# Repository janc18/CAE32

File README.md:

# CAE32

CAE32 is a project for building and developing all stages of a gaming wheel for PC, specifically for the GNU/Linux operating system.

If you want to contribute, please read the [CONTRIBUTING-english.md](./docs/CONTRIBUTING-english.md) file.

Si tu quieres contribuir, por favor lee el documento [CONTRIBUTING.md](./CONTRIBUTING.md)  

## Overall current status

Developing the UML diagram of the whole system

### PCBs

### Firmware

Working on the development of the UML diagram for the pedals  firmware

### Software

Needed the improvement of compilation and flags for the user interface

## The stages include:

* PCB Design
* Firmware
* Driver (Kernel module if necessary)
* Configuration and calibration through a graphical user interface (GTK-3)
* Design of mechanisms for pedals, gear lever, and wheel
* Power PCB design for feedback motor control (FFB)

### PCB Sponsored by PCBWay

The PCB quality is excellent, the contact with the support service is good, they responded very quickly in the case of any issue, 
and it has a good PCB finish using the STM assembly service,  all the IC pads are correctly soldered. Overall, the total cost of 5 PCBs 
and 2 PCBs with the assembly service is a very accessible, so I will keep using PCBWAY to build the next PCB iterations

[PCBWay Webpage](https://www.pcbway.com/)

## Programming Frameworks and Tools

* Espressif (ESP-IDF)
* STM32CubeIDE
* STM32CubeProgrammer

### User Interface

The interface is developed with the GTK 3 framework, which will allow configurations such as:

* Visualization of data graphically and textually (console)
* Transmission type (Manual, Automatic, Sequential, custom) **Natively**
* Pedal limits, sensitivity
* Pedal type
  * Analog input (Potentiometer, Hall effect, and load cell)
  * SPI, I2C input (Custom sensor)
* Firmware update

## How to compile the project

1. Install all the dependencies
```bash
sudo apt install cmake make gcc pkgconf libevdev-dev libgtk-3-dev libgtk-3-0 libgtest-dev g++
```

2. Run the script to check if all the dependencies was successfully installed
```bash
./Source_code/checking_dependency.sh
```
3. Execute the Makefile to build the graphic interface and the unit tests
```sh
make -C Source_code/
```

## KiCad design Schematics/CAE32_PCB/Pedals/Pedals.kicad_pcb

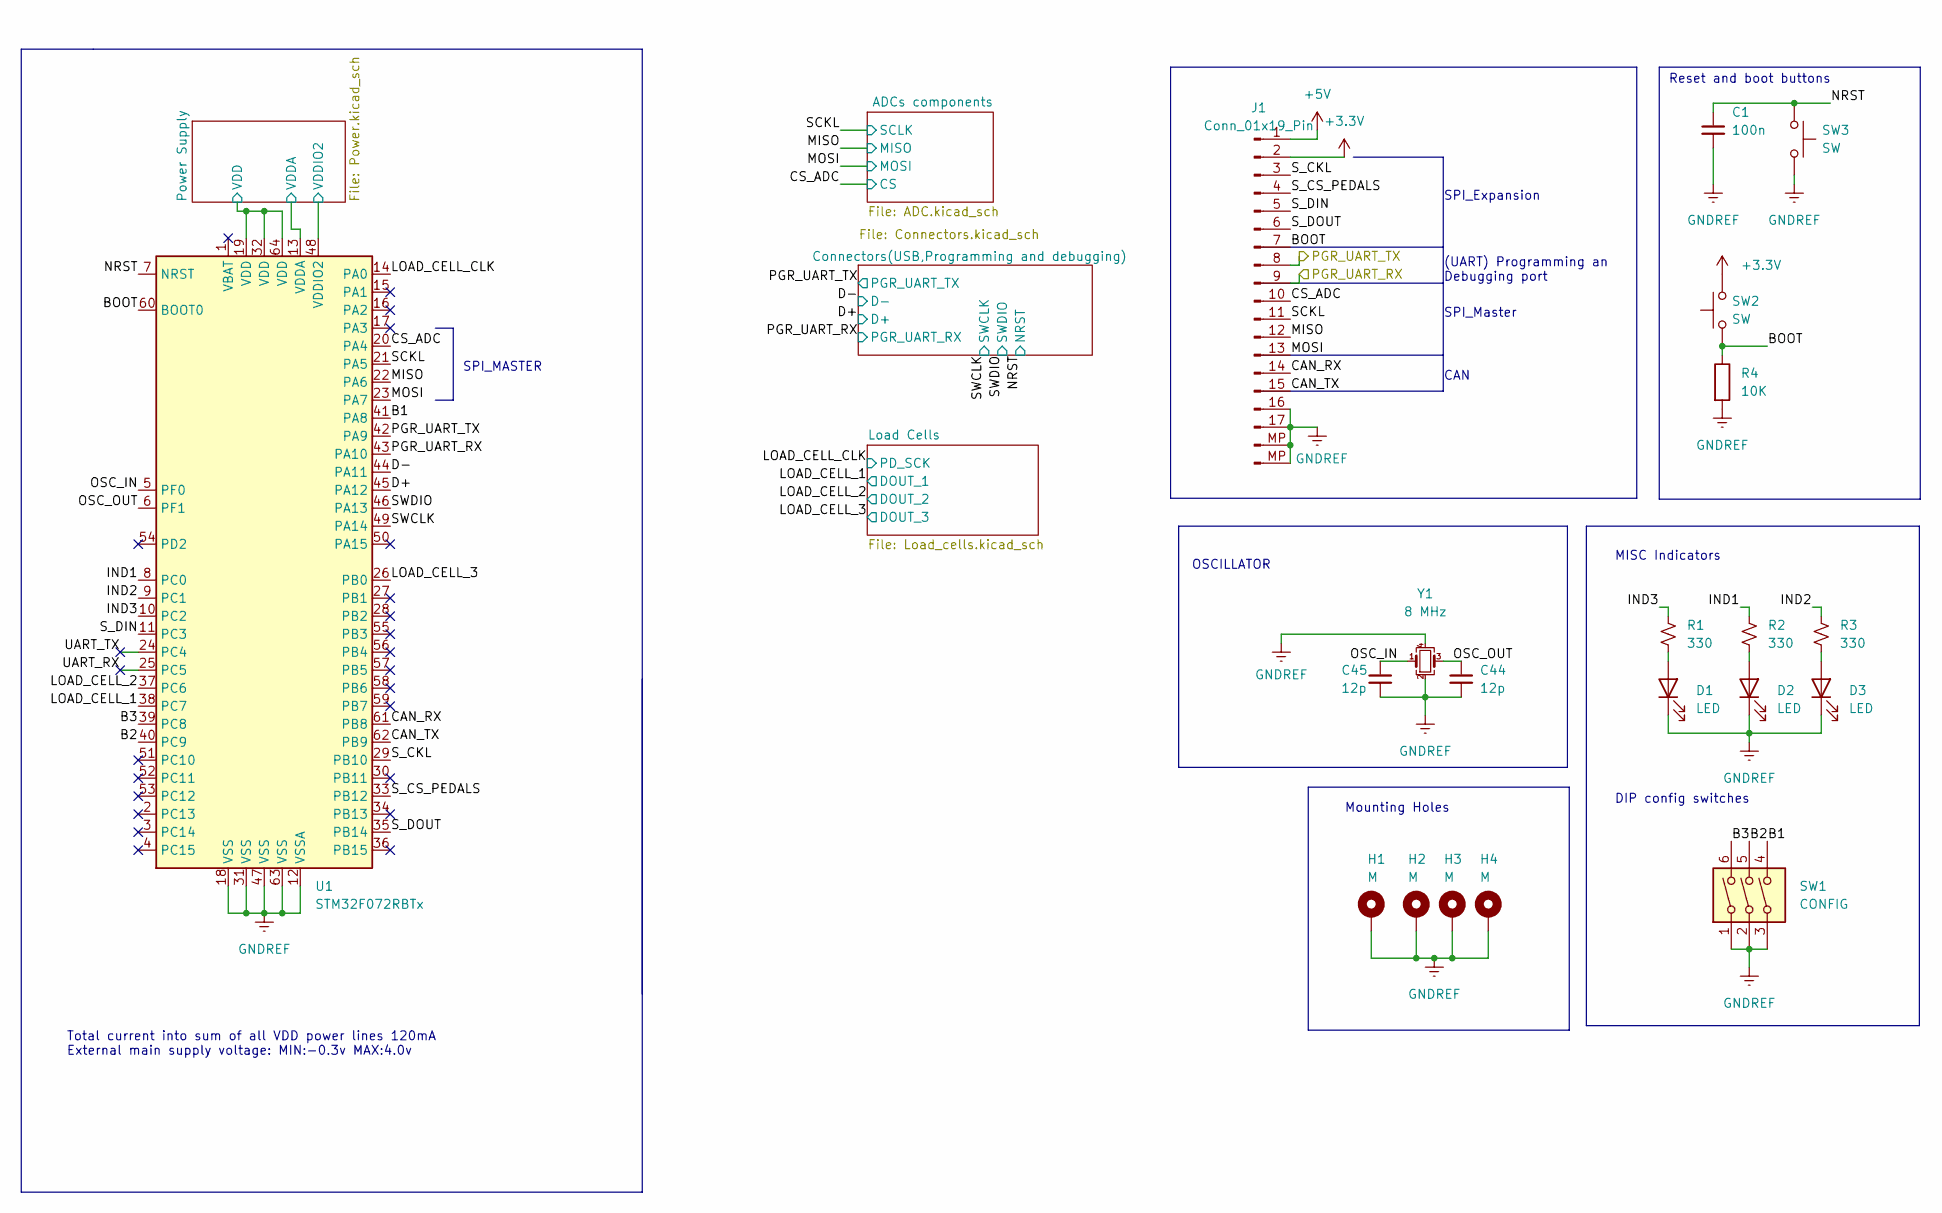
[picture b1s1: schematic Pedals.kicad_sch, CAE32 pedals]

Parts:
C1: 100n; C_0603_1608Metric; LCSC_PART C66501
C44, C45: 12p; C_0603_1608Metric; LCSC_PART C882527
D1, D2, D3: LED; LED_0805_2012Metric; LCSC_PART C965815
H1, H2, H3, H4: M; MountingHole_3.2mm_M3_DIN965_Pad_TopBottom
J1: Conn_01x19_Pin; TE_1-84953-7_1x17-1MP_P1.0mm_Horizontal; LCSC_PART C500176
R1, R2, R3: 330; R_0603_1608Metric; LCSC_PART C21190
R4: 10K; R_0603_1608Metric; LCSC_PART C25804
SW1: CONFIG; SW_DIP_SPSTx03_Slide_KingTek_DSHP03TJ_W5.25mm_P1.27mm_JPin; LCSC_PART C5289932
SW2, SW3: SW; SW_SPST_TL3342; LCSC_PART C2886897
U1: STM32F072RBTx; LQFP-64_10x10mm_P0.5mm; LCSC_PART C46046
Y1: 8 MHz; Crystal_SMD_3225-4Pin_3.2x2.5mm; LCSC_PART C2682775

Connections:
+3.3V: J1.2, SW2.2, U1.13 (VDDA), U1.19 (VDD), U1.32 (VDD), U1.48 (VDDIO2), U1.64 (VDD); also elsewhere on the board
+5V: J1.1; also elsewhere on the board
/B1: SW1.4, U1.41 (PA8)
/B2: SW1.5, U1.40 (PC9)
/B3: SW1.6, U1.39 (PC8)
/BOOT: J1.7, R4.1, SW2.1, U1.60 (BOOT0)
/CAN_RX: J1.14, U1.61 (PB8)
/CAN_TX: J1.15, U1.62 (PB9)
/CS_ADC: J1.10, U1.20 (PA4); also elsewhere on the board
/D+: U1.45 (PA12); also elsewhere on the board
/D-: U1.44 (PA11); also elsewhere on the board
/IND1: R2.1, U1.8 (PC0)
/IND2: R3.1, U1.9 (PC1)
/IND3: R1.1, U1.10 (PC2)
/LOAD_CELL_1: U1.38 (PC7); also elsewhere on the board
/LOAD_CELL_2: U1.37 (PC6); also elsewhere on the board
/LOAD_CELL_3: U1.26 (PB0); also elsewhere on the board
/LOAD_CELL_CLK: U1.14 (PA0); also elsewhere on the board
/MISO: J1.12, U1.22 (PA6); also elsewhere on the board
/MOSI: J1.13, U1.23 (PA7); also elsewhere on the board
/NRST: C1.1, SW3.1, U1.7 (NRST); also elsewhere on the board
/OSC_IN: C45.1, U1.5 (PF0), Y1.1
/OSC_OUT: C44.1, U1.6 (PF1), Y1.3
/PGR_UART_RX: J1.9, U1.43 (PA10)
/PGR_UART_TX: J1.8, U1.42 (PA9)
/SCKL: J1.11, U1.21 (PA5); also elsewhere on the board
/SWCLK: U1.49 (PA14); also elsewhere on the board
/SWDIO: U1.46 (PA13); also elsewhere on the board
/S_CKL: J1.3, U1.29 (PB10)
/S_CS_PEDALS: J1.4, U1.33 (PB12)
/S_DIN: J1.5, U1.11 (PC3)
/S_DOUT: J1.6, U1.35 (PB14)
/UART_RX: U1.25 (PC5)
/UART_TX: U1.24 (PC4)
GNDREF: C1.2, C44.2, C45.2, D1.1 (K), D2.1 (K), D3.1 (K), H1.1, H2.1, H3.1, H4.1, J1.16, J1.17, J1.MP, R4.2, SW1.1, SW1.2, SW1.3, SW3.2, U1.12 (VSSA), U1.18 (VSS), U1.31 (VSS), U1.47 (VSS), U1.63 (VSS), Y1.2, Y1.4; also elsewhere on the board
unnamed: D1.2 (A), R1.2
unnamed: D2.2 (A), R2.2
unnamed: D3.2 (A), R3.2

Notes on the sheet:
(UART) Programming an Debugging port
OSCILLATOR
CAN
SPI_MASTER
DIP config switches
SPI_Expansion
Mounting Holes
Total current into sum of all VDD power lines 120mA External main supply voltage: MIN:-0.3v MAX:4.0v
MISC Indicators
SPI_Master
Reset and boot buttons

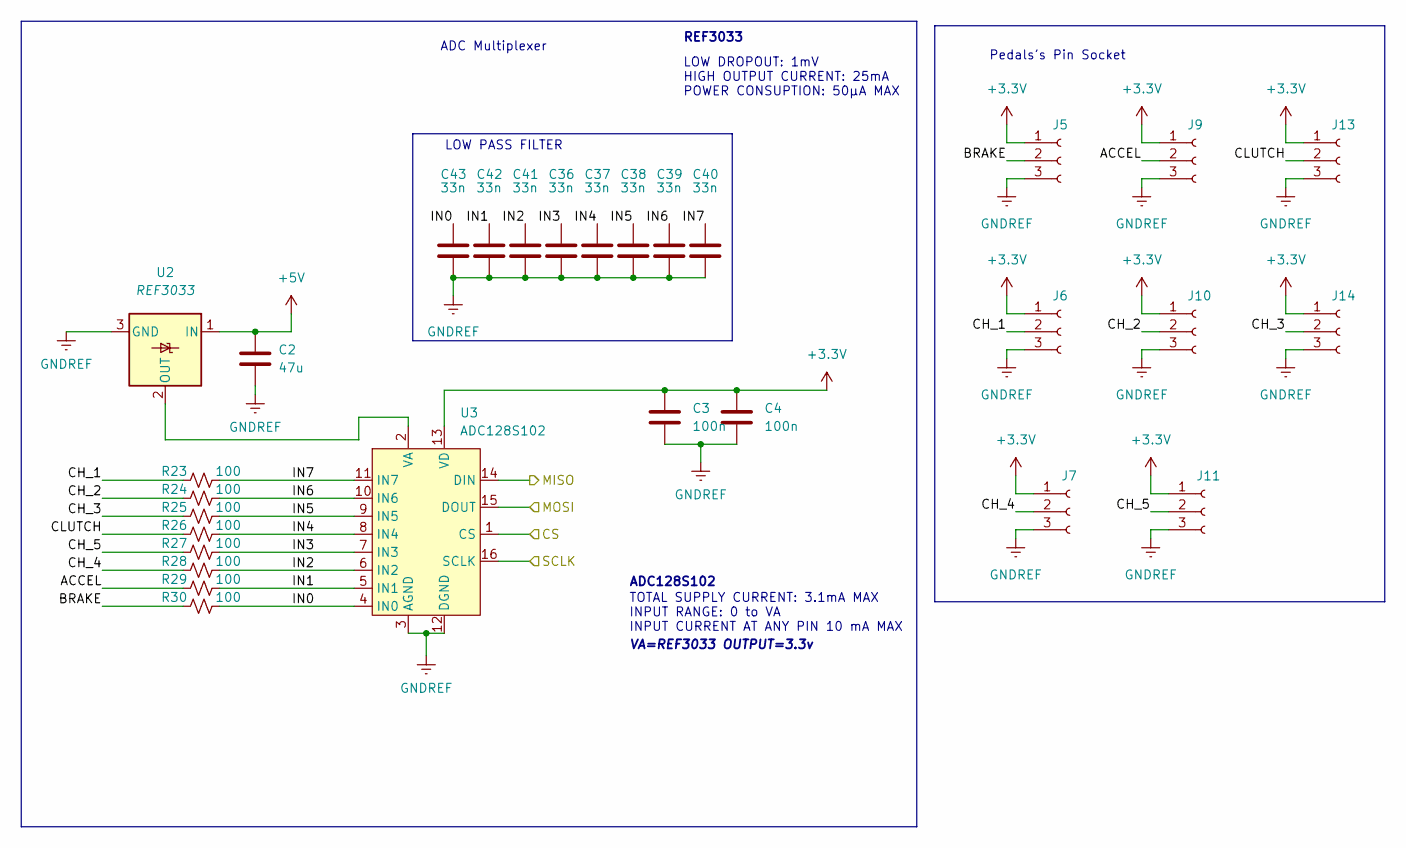
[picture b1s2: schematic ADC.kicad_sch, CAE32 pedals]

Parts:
C2: 47u; C_0603_1608Metric; LCSC_PART C140782
C3, C4: 100n; C_0603_1608Metric; LCSC_PART C66501
C36, C37, C38, C39, C40, C41, C42, C43: 33n; C_0603_1608Metric; LCSC_PART C21117
J5, J6, J7, J9, J10, J11, J13, J14: Conn_01x03_Female; PinHeader_1x03_P2.54mm_Vertical; LCSC_PART C6332196
R23, R24, R25, R26, R27, R28, R29, R30: 100; R_0603_1608Metric; LCSC_PART C25201
U2: REF3033; SOT-23; LCSC_PART C36658
U3: ADC128S102; TSSOP-16_4.4x5mm_P0.65mm

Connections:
+3.3V: C3.1, C4.1, J5.1, J6.1, J7.1, J9.1, J10.1, J11.1, J13.1, J14.1, U3.13 (VD); also elsewhere on the board
+5V: C2.1, U2.1 (IN); also elsewhere on the board
/ADCs components/ACCEL: J9.2, R29.1
/ADCs components/BRAKE: J5.2, R30.1
/ADCs components/CH_1: J6.2, R23.1
/ADCs components/CH_2: J10.2, R24.1
/ADCs components/CH_3: J14.2, R25.1
/ADCs components/CH_4: J7.2, R28.1
/ADCs components/CH_5: J11.2, R27.1
/ADCs components/CLUTCH: J13.2, R26.1
/ADCs components/IN0: C43.1, R30.2, U3.4 (IN0)
/ADCs components/IN1: C42.1, R29.2, U3.5 (IN1)
/ADCs components/IN2: C41.1, R28.2, U3.6 (IN2)
/ADCs components/IN3: C36.1, R27.2, U3.7 (IN3)
/ADCs components/IN4: C37.1, R26.2, U3.8 (IN4)
/ADCs components/IN5: C38.1, R25.2, U3.9 (IN5)
/ADCs components/IN6: C39.1, R24.2, U3.10 (IN6)
/ADCs components/IN7: C40.1, R23.2, U3.11 (IN7)
/CS_ADC: U3.1 (CS); also elsewhere on the board
/MISO: U3.14 (DIN); also elsewhere on the board
/MOSI: U3.15 (DOUT); also elsewhere on the board
/SCKL: U3.16 (SCLK); also elsewhere on the board
GNDREF: C2.2, C3.2, C4.2, C36.2, C37.2, C38.2, C39.2, C40.2, C41.2, C42.2, C43.2, J5.3, J6.3, J7.3, J9.3, J10.3, J11.3, J13.3, J14.3, U2.3 (GND), U3.3 (AGND), U3.12 (DGND); also elsewhere on the board
unnamed: U2.2 (OUT), U3.2 (VA)

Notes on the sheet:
LOW DROPOUT: 1mV HIGH OUTPUT CURRENT: 25mA POWER CONSUPTION: 50μA MAX
ADC Multiplexer
VA=REF3033 OUTPUT=3.3v
ADC128S102
Pedals's Pin Socket
LOW PASS FILTER
REF3033
TOTAL SUPPLY CURRENT: 3.1mA MAX INPUT RANGE: 0 to VA INPUT CURRENT AT ANY PIN 10 mA MAX

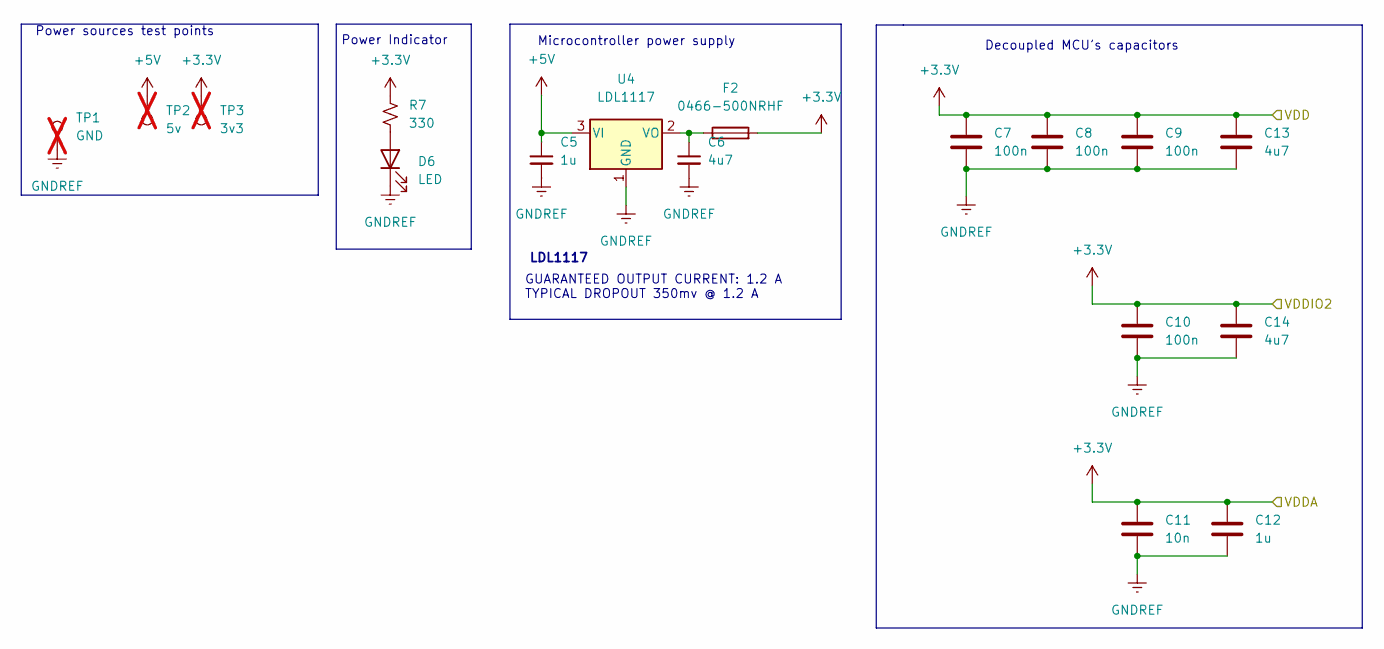
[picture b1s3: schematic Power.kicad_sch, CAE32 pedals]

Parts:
C5, C12: 1u; C_0603_1608Metric; LCSC_PART C1592
C6, C13, C14: 4u7; C_0603_1608Metric; LCSC_PART C1705
C7, C8, C9, C10: 100n; C_0603_1608Metric; LCSC_PART C66501
C11: 10n; C_0603_1608Metric; LCSC_PART C100042
D6: LED; LED_0805_2012Metric; LCSC_PART C965815
F2: 0466-500NRHF; Fuse_1206_3216Metric; LCSC_PART C151133
R7: 330; R_0603_1608Metric; LCSC_PART C21190
TP1: GND; TestPoint_Pad_D1.0mm; not fitted
TP2: 5v; TestPoint_Pad_D1.0mm; not fitted
TP3: 3v3; TestPoint_Pad_D1.0mm; not fitted
U4: LDL1117; SOT-223-3_TabPin2; LCSC_PART C2798214

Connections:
+3.3V: C7.1, C8.1, C9.1, C10.1, C11.1, C12.1, C13.1, C14.1, F2.2, R7.1, TP3.1; also elsewhere on the board
+5V: C5.1, TP2.1, U4.3 (VI); also elsewhere on the board
GNDREF: C5.2, C6.2, C7.2, C8.2, C9.2, C10.2, C11.2, C12.2, C13.2, C14.2, D6.1 (K), TP1.1, U4.1 (GND); also elsewhere on the board
unnamed: D6.2 (A), R7.2
unnamed: C6.1, F2.1, U4.2 (VO)

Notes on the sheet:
Decoupled MCU's capacitors
Power Indicator
GUARANTEED OUTPUT CURRENT: 1.2 A TYPICAL DROPOUT 350mv @ 1.2 A
Microcontroller power supply
Power sources test points
LDL1117

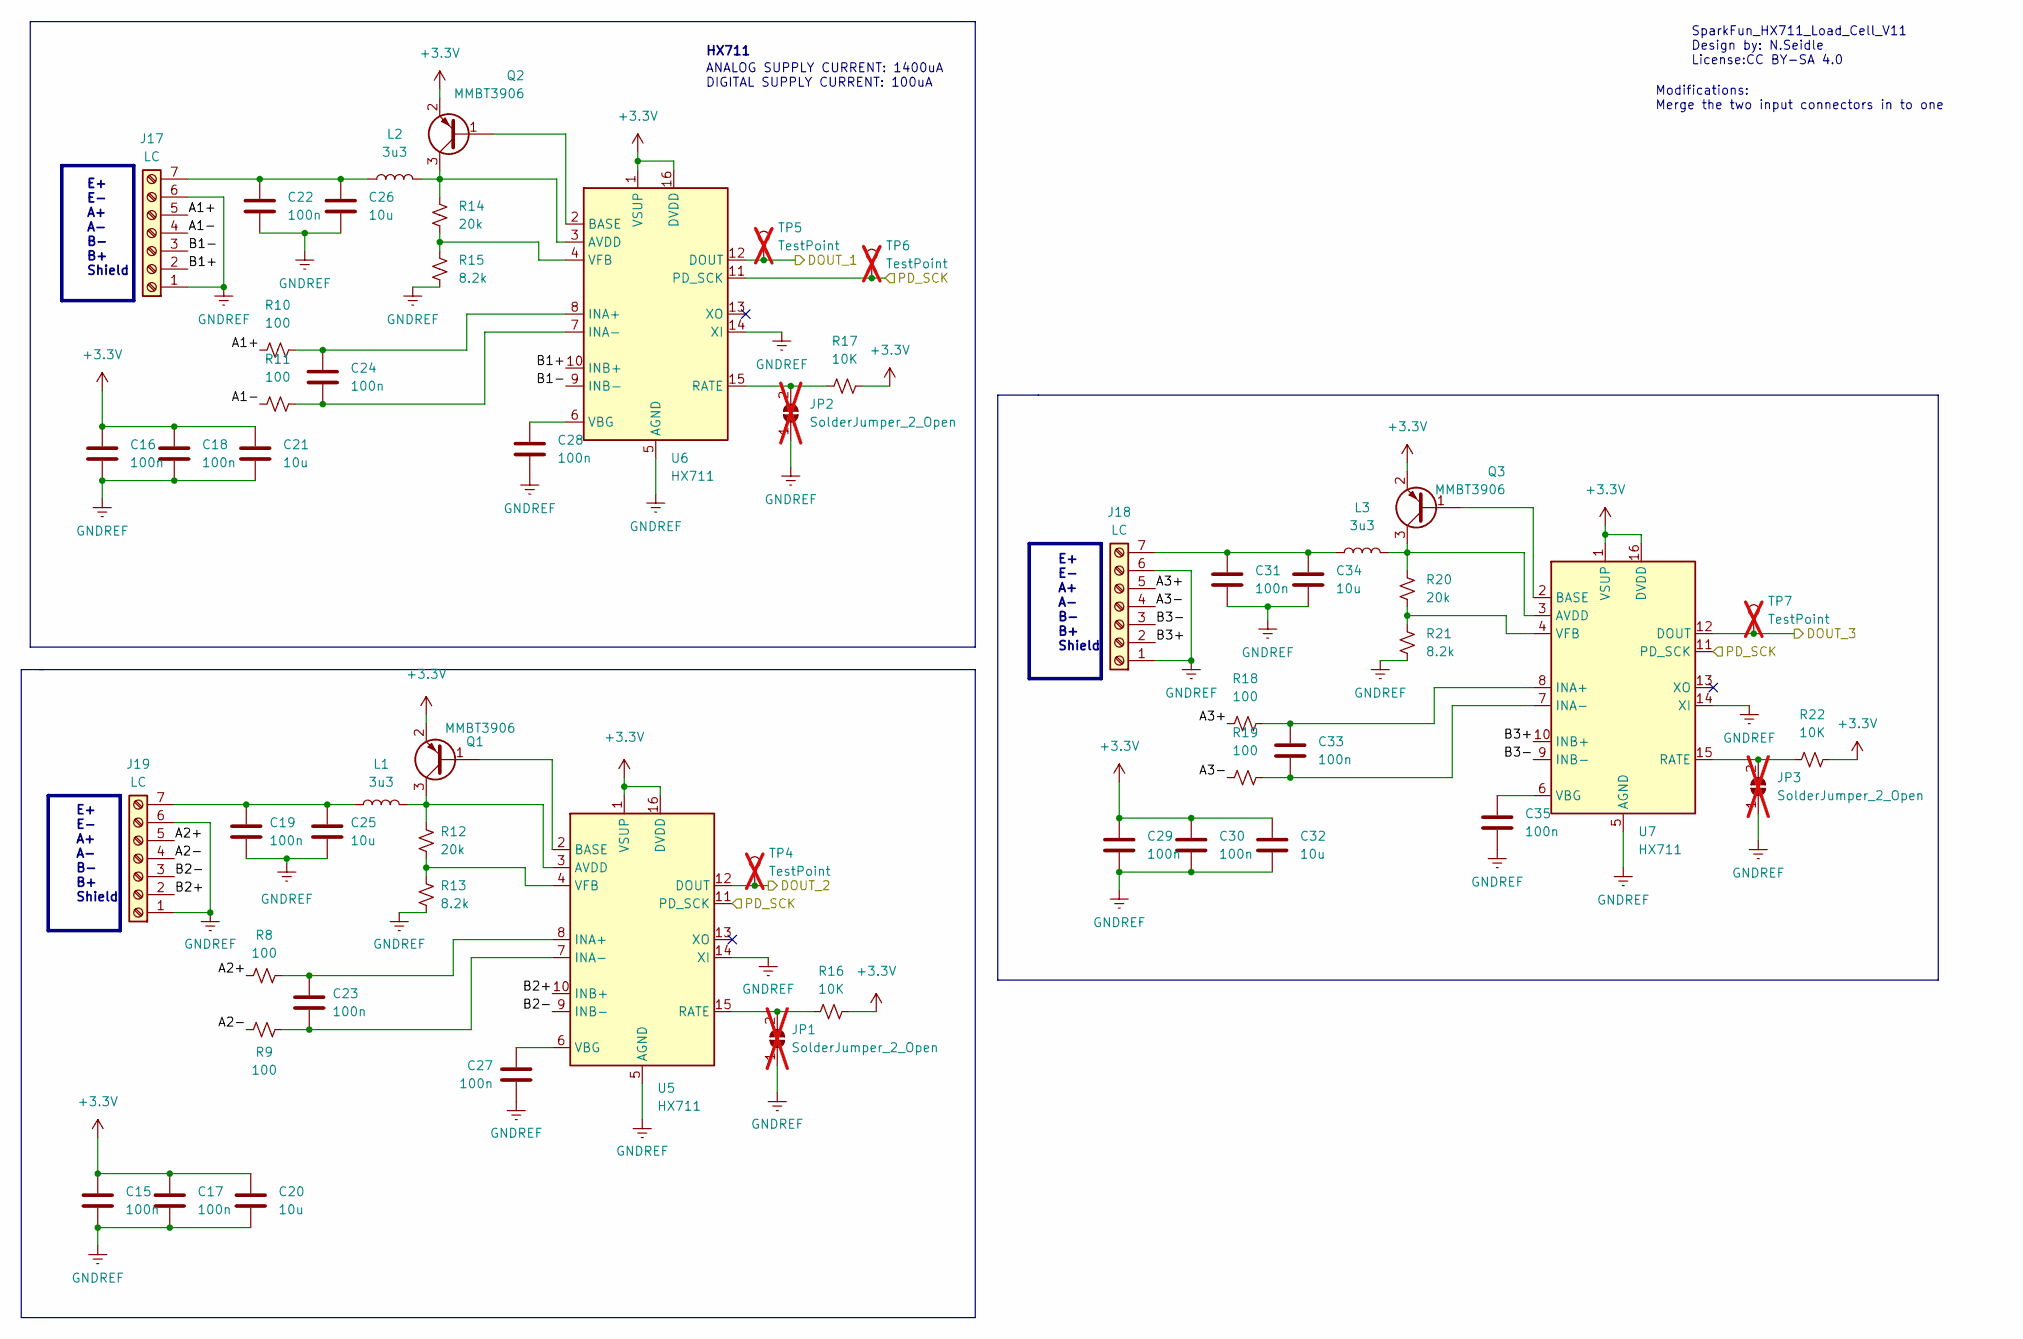
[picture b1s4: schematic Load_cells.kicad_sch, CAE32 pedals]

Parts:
C15, C16, C17, C18, C19, C22, C23, C24, C27, C28, C29, C30, C31, C33, C35: 100n; C_0603_1608Metric; LCSC_PART C66501
C20, C21, C25, C26, C32, C34: 10u; C_0603_1608Metric; LCSC_PART C1691
J17, J18, J19: LC; TerminalBlock_TE_282834-7_1x07_P2.54mm_Horizontal; LCSC_PART C915916
JP1, JP2, JP3: SolderJumper_2_Open; SolderJumper-2_P1.3mm_Open_RoundedPad1.0x1.5mm; not fitted
L1, L2, L3: 3u3; L_0402_1005Metric; LCSC_PART C84474
Q1, Q2, Q3: MMBT3906; SOT-23
R8, R9, R10, R11, R18, R19: 100; R_0603_1608Metric; LCSC_PART C25201
R12, R14, R20: 20k; R_0603_1608Metric; LCSC_PART C4184
R13, R15, R21: 8.2k; R_0603_1608Metric; LCSC_PART C114637
R16, R17, R22: 10K; R_0603_1608Metric; LCSC_PART C25804
TP4, TP5, TP6, TP7: TestPoint; TestPoint_Pad_D1.0mm; not fitted
U5, U6, U7: HX711; SOP-16_3.9x9.9mm_P1.27mm; LCSC_PART C43656

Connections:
+3.3V: C15.1, C16.1, C17.1, C18.1, C20.1, C21.1, C29.1, C30.1, C32.1, Q1.2 (E), Q2.2 (E), Q3.2 (E), R16.2, R17.2, R22.2, U5.1 (VSUP), U5.16 (DVDD), U6.1 (VSUP), U6.16 (DVDD), U7.1 (VSUP), U7.16 (DVDD); also elsewhere on the board
/LOAD_CELL_1: TP5.1, U6.12 (DOUT); also elsewhere on the board
/LOAD_CELL_2: TP4.1, U5.12 (DOUT); also elsewhere on the board
/LOAD_CELL_3: TP7.1, U7.12 (DOUT); also elsewhere on the board
/LOAD_CELL_CLK: TP6.1, U5.11 (PD_SCK), U6.11 (PD_SCK), U7.11 (PD_SCK); also elsewhere on the board
/Load Cells/A1+: J17.5, R10.1
/Load Cells/A1-: J17.4, R11.2
/Load Cells/A2+: J19.5, R8.1
/Load Cells/A2-: J19.4, R9.2
/Load Cells/A3+: J18.5, R18.1
/Load Cells/A3-: J18.4, R19.2
/Load Cells/B1+: J17.2, U6.10 (INB+)
/Load Cells/B1-: J17.3, U6.9 (INB-)
/Load Cells/B2+: J19.2, U5.10 (INB+)
/Load Cells/B2-: J19.3, U5.9 (INB-)
/Load Cells/B3+: J18.2, U7.10 (INB+)
/Load Cells/B3-: J18.3, U7.9 (INB-)
GNDREF: C15.2, C16.2, C17.2, C18.2, C19.2, C20.2, C21.2, C22.2, C25.2, C26.2, C27.2, C28.2, C29.2, C30.2, C31.2, C32.2, C34.2, C35.2, J17.1, J17.6, J18.1, J18.6, J19.1, J19.6, JP1.1 (A), JP2.1 (A), JP3.1 (A), R13.2, R15.2, R21.2, U5.5 (AGND), U5.14 (XI), U6.5 (AGND), U6.14 (XI), U7.5 (AGND), U7.14 (XI); also elsewhere on the board
unnamed: C22.1, C26.1, J17.7, L2.1
unnamed: C31.1, C34.1, J18.7, L3.1
unnamed: C19.1, C25.1, J19.7, L1.1
unnamed: JP1.2 (B), R16.1, U5.15 (RATE)
unnamed: JP2.2 (B), R17.1, U6.15 (RATE)
unnamed: JP3.2 (B), R22.1, U7.15 (RATE)
unnamed: Q1.1 (B), U5.2 (BASE)
unnamed: L1.2, Q1.3 (C), R12.1, U5.3 (AVDD)
unnamed: Q2.1 (B), U6.2 (BASE)
unnamed: L2.2, Q2.3 (C), R14.1, U6.3 (AVDD)
unnamed: Q3.1 (B), U7.2 (BASE)
unnamed: L3.2, Q3.3 (C), R20.1, U7.3 (AVDD)
unnamed: C23.1, R8.2, U5.8 (INA+)
unnamed: C23.2, R9.1, U5.7 (INA-)
unnamed: C27.1, U5.6 (VBG)
unnamed: R12.2, R13.1, U5.4 (VFB)
unnamed: C24.1, R10.2, U6.8 (INA+)
unnamed: C24.2, R11.1, U6.7 (INA-)
unnamed: C28.1, U6.6 (VBG)
unnamed: R14.2, R15.1, U6.4 (VFB)
unnamed: C33.1, R18.2, U7.8 (INA+)
unnamed: C33.2, R19.1, U7.7 (INA-)
unnamed: C35.1, U7.6 (VBG)
unnamed: R20.2, R21.1, U7.4 (VFB)

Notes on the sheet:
HX711
SparkFun_HX711_Load_Cell_V11 Design by: N.Seidle License:CC BY-SA 4.0
E+ E- A+ A- B- B+ Shield
ANALOG SUPPLY CURRENT: 1400uA DIGITAL SUPPLY CURRENT: 100uA
Modifications: Merge the two input connectors in to one

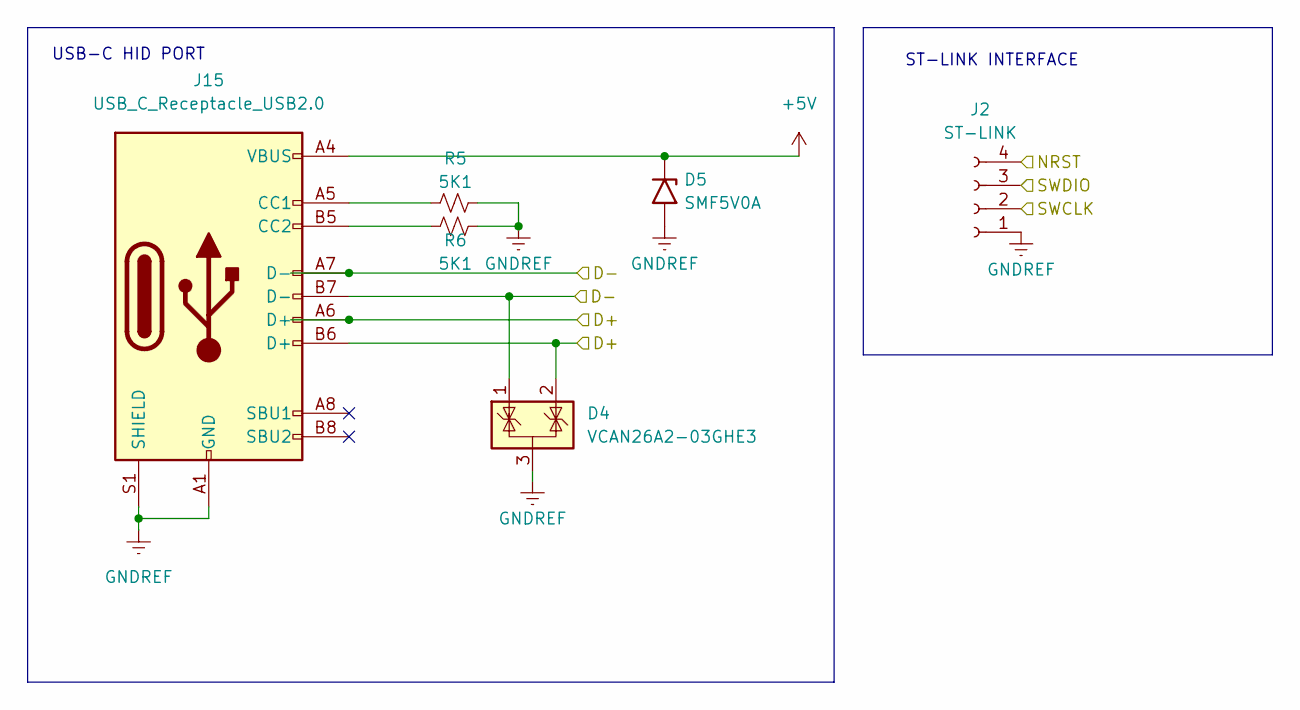
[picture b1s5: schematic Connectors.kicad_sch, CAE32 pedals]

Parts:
D4: VCAN26A2-03GHE3; SOT-323_SC-70; LCSC_PART C413455
D5: SMF5V0A; D_SOD-123; LCSC_PART C908213
J2: ST-LINK; PinSocket_1x04_P2.54mm_Vertical
J15: USB_C_Receptacle_USB2.0; USB_C_Receptacle_HRO_TYPE-C-31-M-12
R5, R6: 5K1; R_0603_1608Metric

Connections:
+5V: D5.1 (A1), J15.A4 (VBUS), J15.A9 (VBUS), J15.B4 (VBUS), J15.B9 (VBUS); also elsewhere on the board
/D+: D4.2 (K), J15.A6 (D+), J15.B6 (D+); also elsewhere on the board
/D-: D4.1 (K), J15.A7 (D-), J15.B7 (D-); also elsewhere on the board
/NRST: J2.4; also elsewhere on the board
/SWCLK: J2.2; also elsewhere on the board
/SWDIO: J2.3; also elsewhere on the board
GNDREF: D4.3 (A), D5.2 (A2), J2.1, J15.A1 (GND), J15.A12 (GND), J15.B1 (GND), J15.B12 (GND), J15.S1 (SHIELD), R5.2, R6.2; also elsewhere on the board
unnamed: J15.A5 (CC1), R5.1
unnamed: J15.B5 (CC2), R6.1

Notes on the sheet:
USB-C HID PORT
ST-LINK INTERFACE

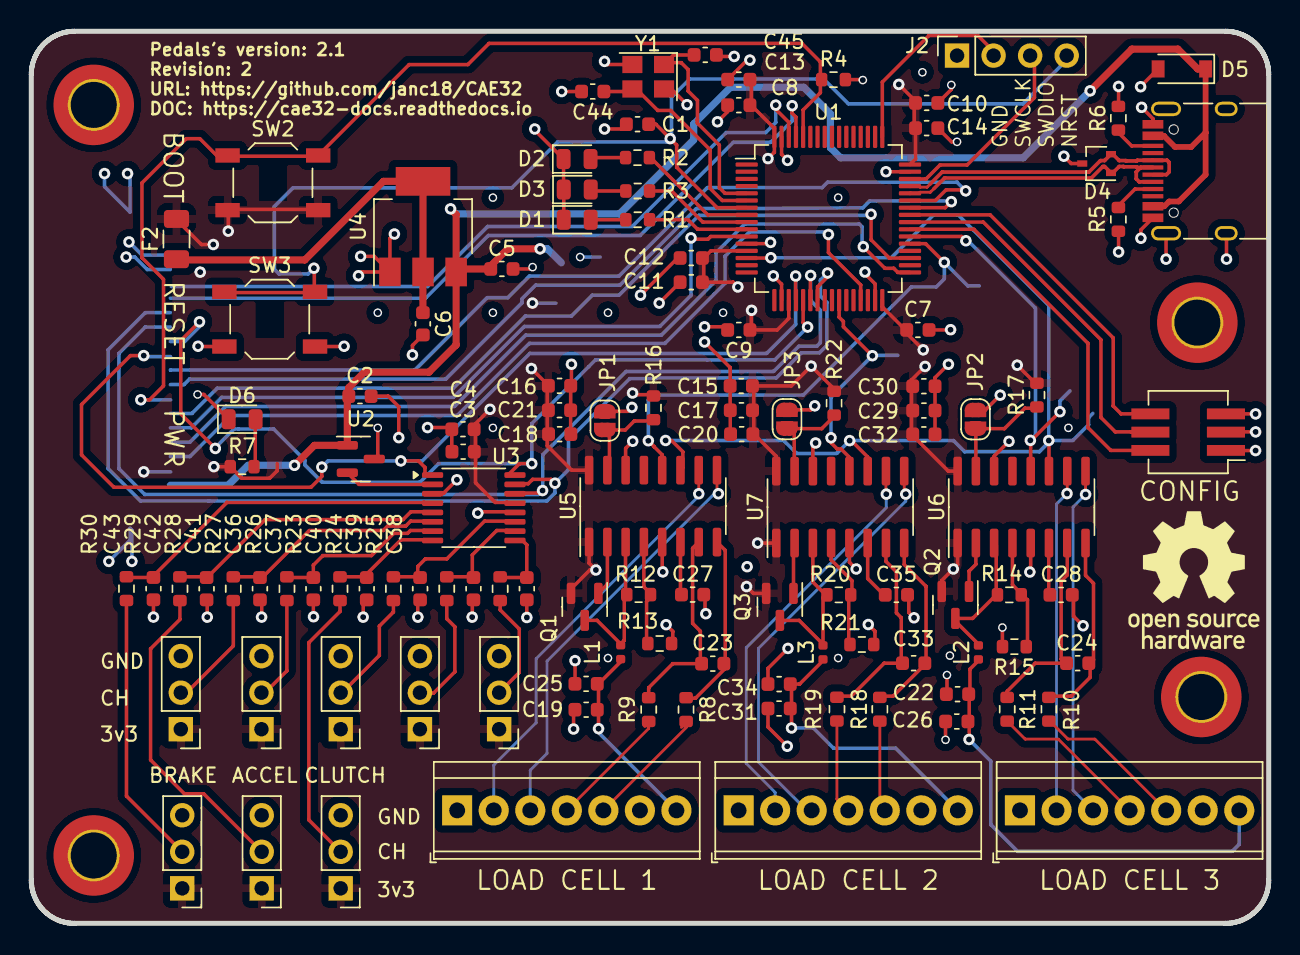
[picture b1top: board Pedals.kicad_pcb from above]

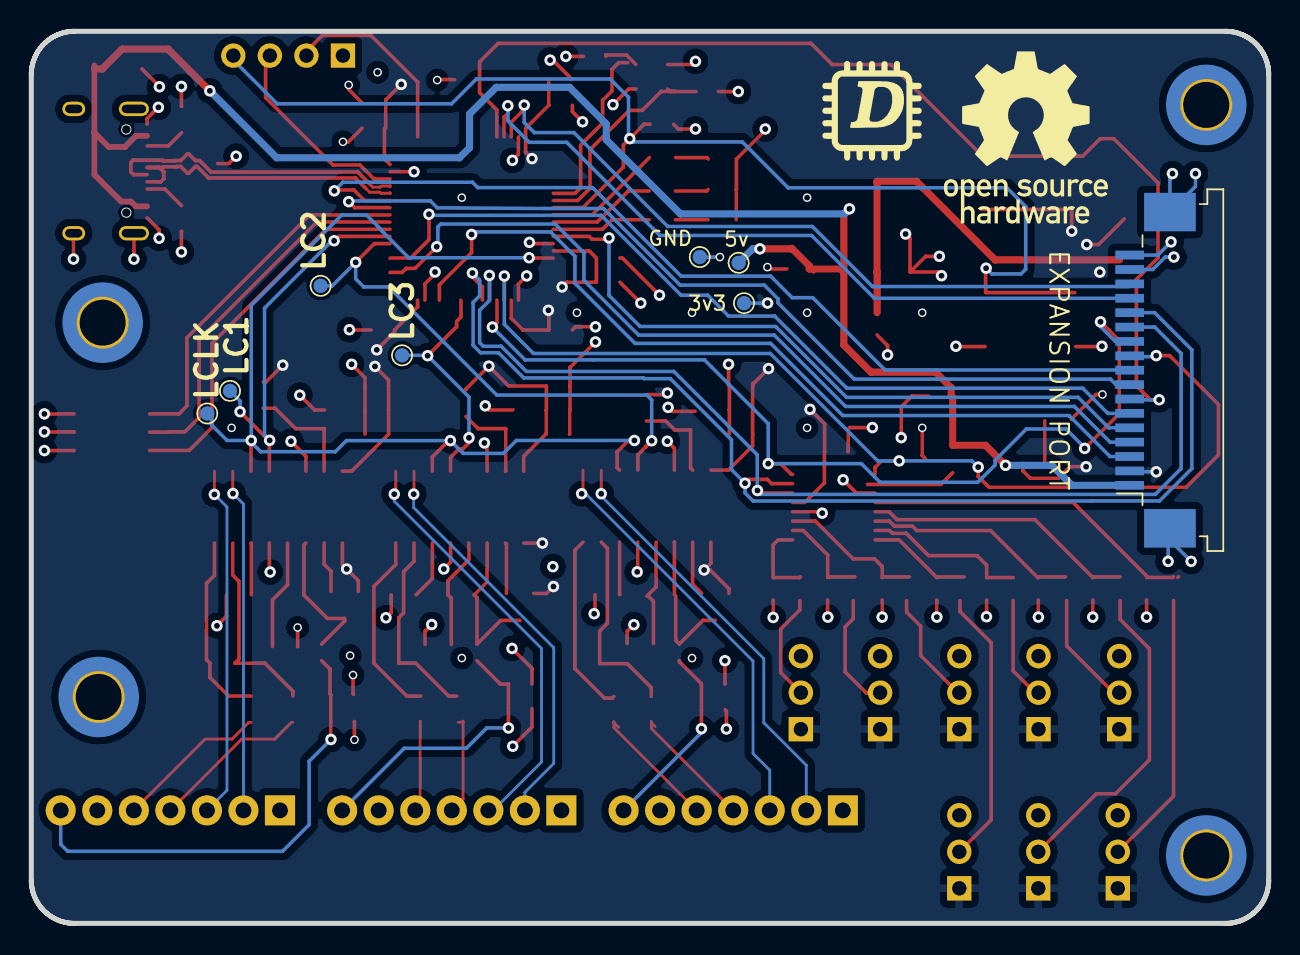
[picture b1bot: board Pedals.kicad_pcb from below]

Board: 4 copper layers, 86.0 x 62.0 mm, 127 parts (8 on the bottom side), 93 nets.

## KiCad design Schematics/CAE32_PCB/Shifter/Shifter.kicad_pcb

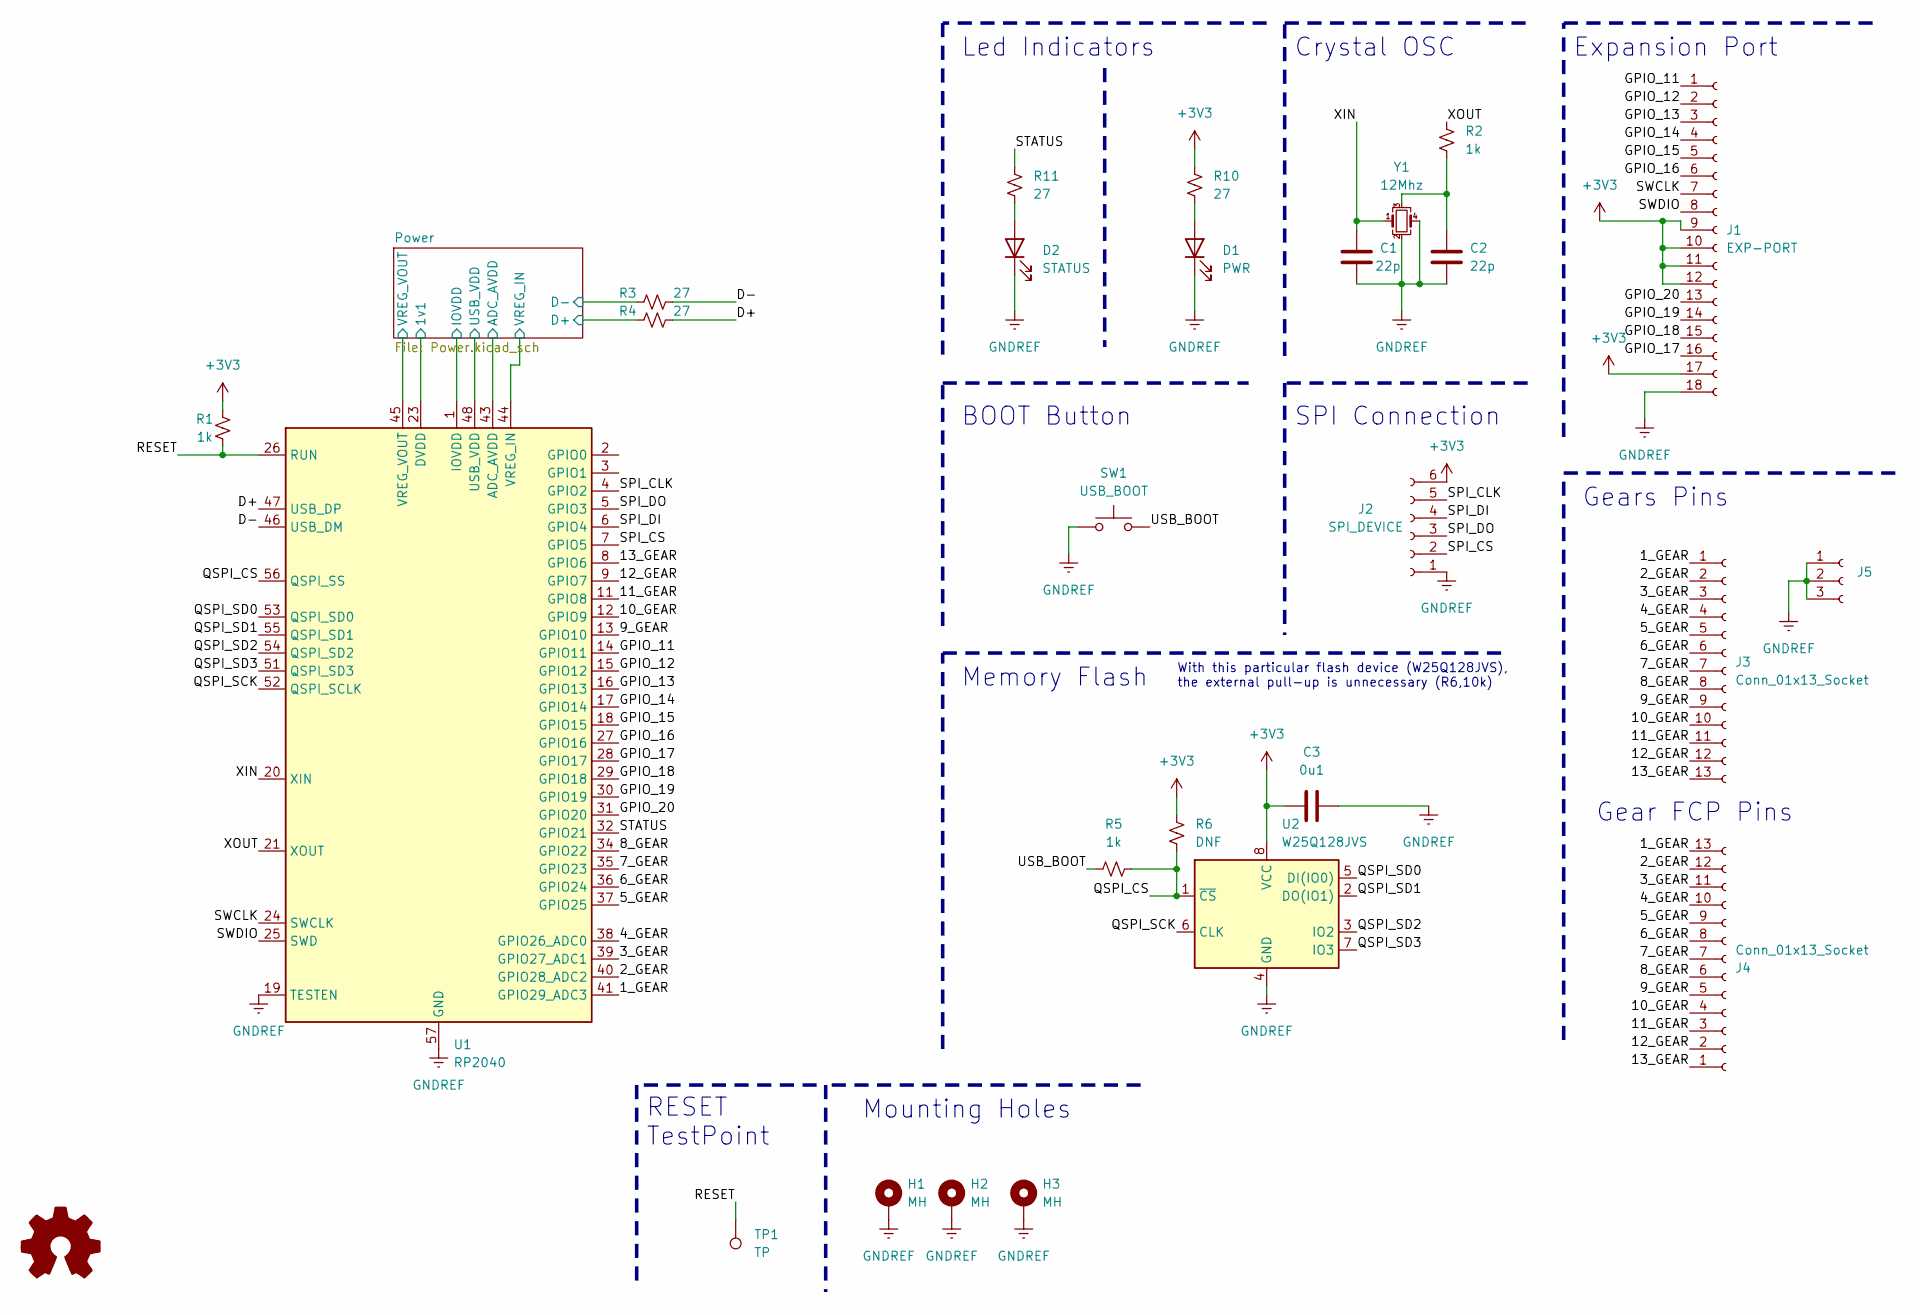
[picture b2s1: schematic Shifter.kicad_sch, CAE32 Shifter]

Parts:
C1, C2: 22p; C_01005_0402Metric
C3: 0u1; C_01005_0402Metric
D1: PWR; LED_0402_1005Metric
D2: STATUS; LED_0402_1005Metric
H1, H2, H3: MH; MountingHole_2.7mm_M2.5_Pad_Via
J1: EXP-PORT; Hirose_FH12-18S-0.5SH_1x18-1MP_P0.50mm_Horizontal
J2: SPI_DEVICE; PinSocket_2x03_P2.54mm_Vertical
J3: Conn_01x13_Socket; Pad_1x13_THT_1.27mm
J4: Conn_01x13_Socket; Hirose_FH12-13S-0.5SH_1x13-1MP_P0.50mm_Horizontal
J5: Conn_01x03_Socket; PinHeader_1x03_P2.54mm_Vertical
R1, R2, R5: 1k; R_0402_1005Metric
R3, R4, R10, R11: 27; R_0402_1005Metric
R6: DNF; R_0402_1005Metric
SW1: USB_BOOT; SW_Push_SPST_NO_Alps_SKRK
TP1: TP; TestPoint_Pad_D1.0mm
U1: RP2040; QFN-56-1EP_7x7mm_P0.4mm_EP3.2x3.2mm
U2: W25Q128JVS; SOIC-8_5.23x5.23mm_P1.27mm
Y1: 12Mhz; Crystal_SMD_3225-4Pin_3.2x2.5mm

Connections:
+3V3: C3.1, J1.9, J1.10, J1.11, J1.12, J1.17, J2.6, R1.1, R6.2, R10.1, U1.1 (IOVDD), U1.10 (IOVDD), U1.22 (IOVDD), U1.33 (IOVDD), U1.42 (IOVDD), U1.43 (ADC_AVDD), U1.44 (VREG_IN), U1.45 (VREG_VOUT), U1.48 (USB_VDD), U1.49 (IOVDD), U2.8 (VCC); also elsewhere on the board
/1_GEAR: J3.1, J4.13, U1.41 (GPIO29_ADC3)
/2_GEAR: J3.2, J4.12, U1.40 (GPIO28_ADC2)
/3_GEAR: J3.3, J4.11, U1.39 (GPIO27_ADC1)
/4_GEAR: J3.4, J4.10, U1.38 (GPIO26_ADC0)
/5_GEAR: J3.5, J4.9, U1.37 (GPIO25)
/6_GEAR: J3.6, J4.8, U1.36 (GPIO24)
/7_GEAR: J3.7, J4.7, U1.35 (GPIO23)
/8_GEAR: J3.8, J4.6, U1.34 (GPIO22)
/9_GEAR: J3.9, J4.5, U1.13 (GPIO10)
/10_GEAR: J3.10, J4.4, U1.12 (GPIO9)
/11_GEAR: J3.11, J4.3, U1.11 (GPIO8)
/12_GEAR: J3.12, J4.2, U1.9 (GPIO7)
/13_GEAR: J3.13, J4.1, U1.8 (GPIO6)
/D+: R4.1, U1.47 (USB_DP)
/D-: R3.1, U1.46 (USB_DM)
/GPIO_11: J1.1, U1.14 (GPIO11)
/GPIO_12: J1.2, U1.15 (GPIO12)
/GPIO_13: J1.3, U1.16 (GPIO13)
/GPIO_14: J1.4, U1.17 (GPIO14)
/GPIO_15: J1.5, U1.18 (GPIO15)
/GPIO_16: J1.6, U1.27 (GPIO16)
/GPIO_17: J1.16, U1.28 (GPIO17)
/GPIO_18: J1.15, U1.29 (GPIO18)
/GPIO_19: J1.14, U1.30 (GPIO19)
/GPIO_20: J1.13, U1.31 (GPIO20)
/Power/1v1: U1.23 (DVDD), U1.50 (DVDD); also elsewhere on the board
/Power/D+: R4.2; also elsewhere on the board
/Power/D-: R3.2; also elsewhere on the board
/QSPI_CS: R5.2, R6.1, U1.56 (QSPI_SS), U2.1 (~CS)
/QSPI_SCK: U1.52 (QSPI_SCLK), U2.6 (CLK)
/QSPI_SD0: U1.53 (QSPI_SD0), U2.5 (DI(IO0))
/QSPI_SD1: U1.55 (QSPI_SD1), U2.2 (DO(IO1))
/QSPI_SD2: U1.54 (QSPI_SD2), U2.3 (IO2)
/QSPI_SD3: U1.51 (QSPI_SD3), U2.7 (IO3)
/RESET: R1.2, TP1.1, U1.26 (RUN)
/SPI_CLK: J2.5, U1.4 (GPIO2)
/SPI_CS: J2.2, U1.7 (GPIO5)
/SPI_DI: J2.4, U1.6 (GPIO4)
/SPI_DO: J2.3, U1.5 (GPIO3)
/STATUS: R11.1, U1.32 (GPIO21)
/SWCLK: J1.7, U1.24 (SWCLK)
/SWDIO: J1.8, U1.25 (SWD)
/USB_BOOT: R5.1, SW1.2
/XIN: C1.1, U1.20 (XIN), Y1.1
/XOUT: R2.1, U1.21 (XOUT)
GNDREF: C1.2, C2.2, C3.2, D1.1 (K), D2.1 (K), H1.1, H2.1, H3.1, J1.18, J2.1, J5.1, J5.2, J5.3, SW1.1, U1.19 (TESTEN), U1.57 (GND), U2.4 (GND), Y1.2, Y1.4; also elsewhere on the board
unnamed: C2.1, R2.2, Y1.3
unnamed: D1.2 (A), R10.2
unnamed: D2.2 (A), R11.2

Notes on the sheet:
Expansion Port
Crystal OSC
BOOT Button
Memory Flash
With this particular flash device (W25Q128JVS), the external pull-up is unnecessary (R6,10k)
Gears Pins
SPI Connection
Mounting Holes
Led Indicators
RESET TestPoint
Gear FCP Pins
